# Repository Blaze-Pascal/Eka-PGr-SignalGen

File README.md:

# Eka-PGr-SignalGen

Eka-PGr-SignalGen is a project designed for signal generation circuits, featuring schematic and PCB design using KiCad and simulations in LTSpice. It includes a Bill of Materials for easy component sourcing.
Features:

    KiCad project files for PCB design
    LTSpice simulation files
    BOM generation for parts

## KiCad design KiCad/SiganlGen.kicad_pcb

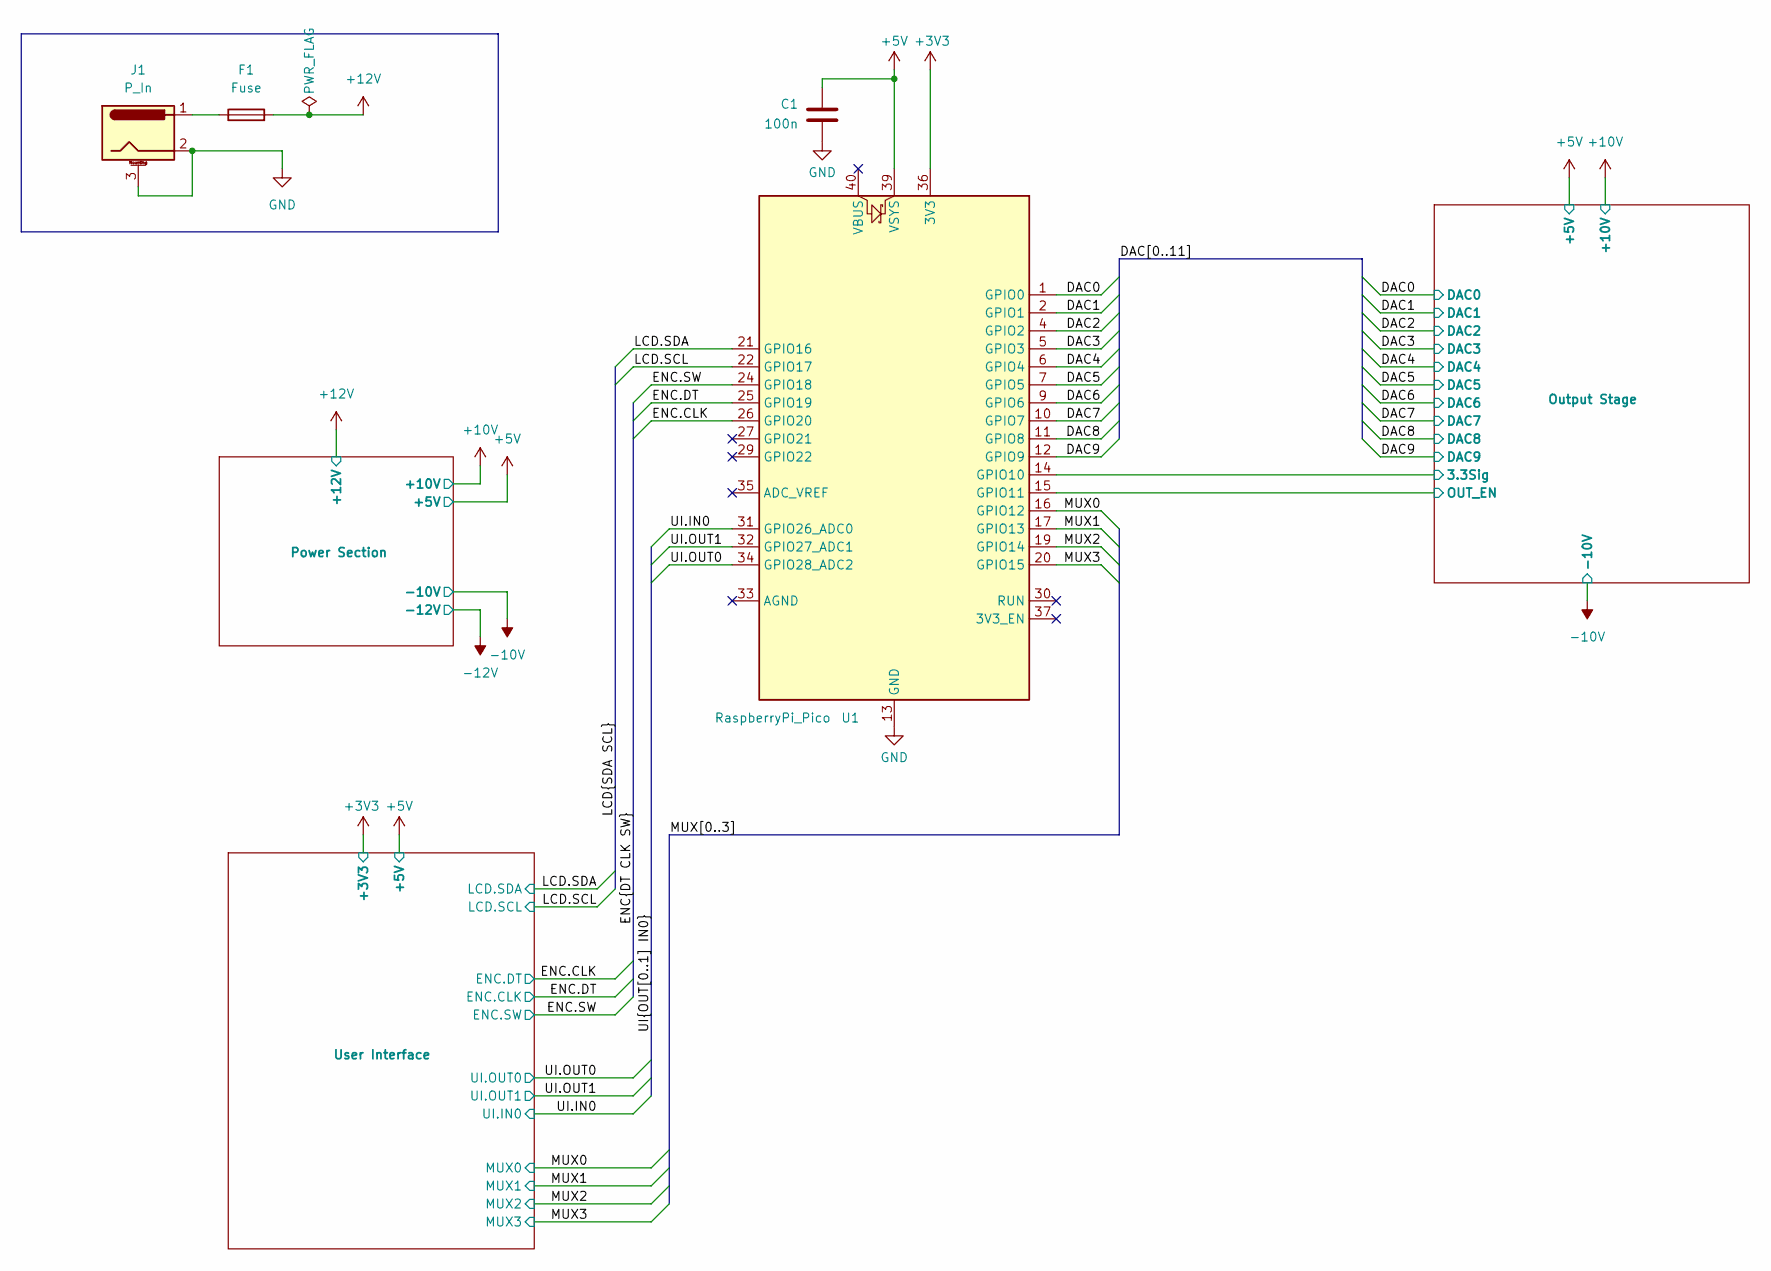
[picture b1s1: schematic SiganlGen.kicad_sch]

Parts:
C1: 100n; C_0805_2012Metric_Pad1.18x1.45mm_HandSolder
F1: Fuse; Fuseholder_Clip-5x20mm_Keystone_3517_Inline_P23.11x6.76mm_D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
J1: P_In; BarrelJack_Horizontal
U1: RaspberryPi_Pico; RaspberryPi_Pico_Common

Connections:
+3V3: U1.36 (3V3); also elsewhere on the board
+5V: C1.1, U1.39 (VSYS); also elsewhere on the board
+12V: F1.2; also elsewhere on the board
/DAC0: U1.1 (GPIO0); also elsewhere on the board
/DAC1: U1.2 (GPIO1); also elsewhere on the board
/DAC2: U1.4 (GPIO2); also elsewhere on the board
/DAC3: U1.5 (GPIO3); also elsewhere on the board
/DAC4: U1.6 (GPIO4); also elsewhere on the board
/DAC5: U1.7 (GPIO5); also elsewhere on the board
/DAC6: U1.9 (GPIO6); also elsewhere on the board
/DAC7: U1.10 (GPIO7); also elsewhere on the board
/DAC8: U1.11 (GPIO8); also elsewhere on the board
/DAC9: U1.12 (GPIO9); also elsewhere on the board
/ENC.CLK: U1.26 (GPIO20); also elsewhere on the board
/ENC.DT: U1.25 (GPIO19); also elsewhere on the board
/ENC.SW: U1.24 (GPIO18); also elsewhere on the board
/LCD.SCL: U1.22 (GPIO17); also elsewhere on the board
/LCD.SDA: U1.21 (GPIO16); also elsewhere on the board
/MUX0: U1.16 (GPIO12); also elsewhere on the board
/MUX1: U1.17 (GPIO13); also elsewhere on the board
/MUX2: U1.19 (GPIO14); also elsewhere on the board
/MUX3: U1.20 (GPIO15); also elsewhere on the board
/Output Stage/3.3Sig: U1.14 (GPIO10); also elsewhere on the board
/Output Stage/OUT_EN: U1.15 (GPIO11); also elsewhere on the board
/UI.IN0: U1.31 (GPIO26_ADC0); also elsewhere on the board
/UI.OUT0: U1.34 (GPIO28_ADC2); also elsewhere on the board
/UI.OUT1: U1.32 (GPIO27_ADC1); also elsewhere on the board
GND: C1.2, J1.2, J1.3 (MountPin), U1.3 (GND), U1.8 (GND), U1.13 (GND), U1.18 (GND), U1.23 (GND), U1.28 (GND), U1.38 (GND); also elsewhere on the board
unnamed: F1.1, J1.1

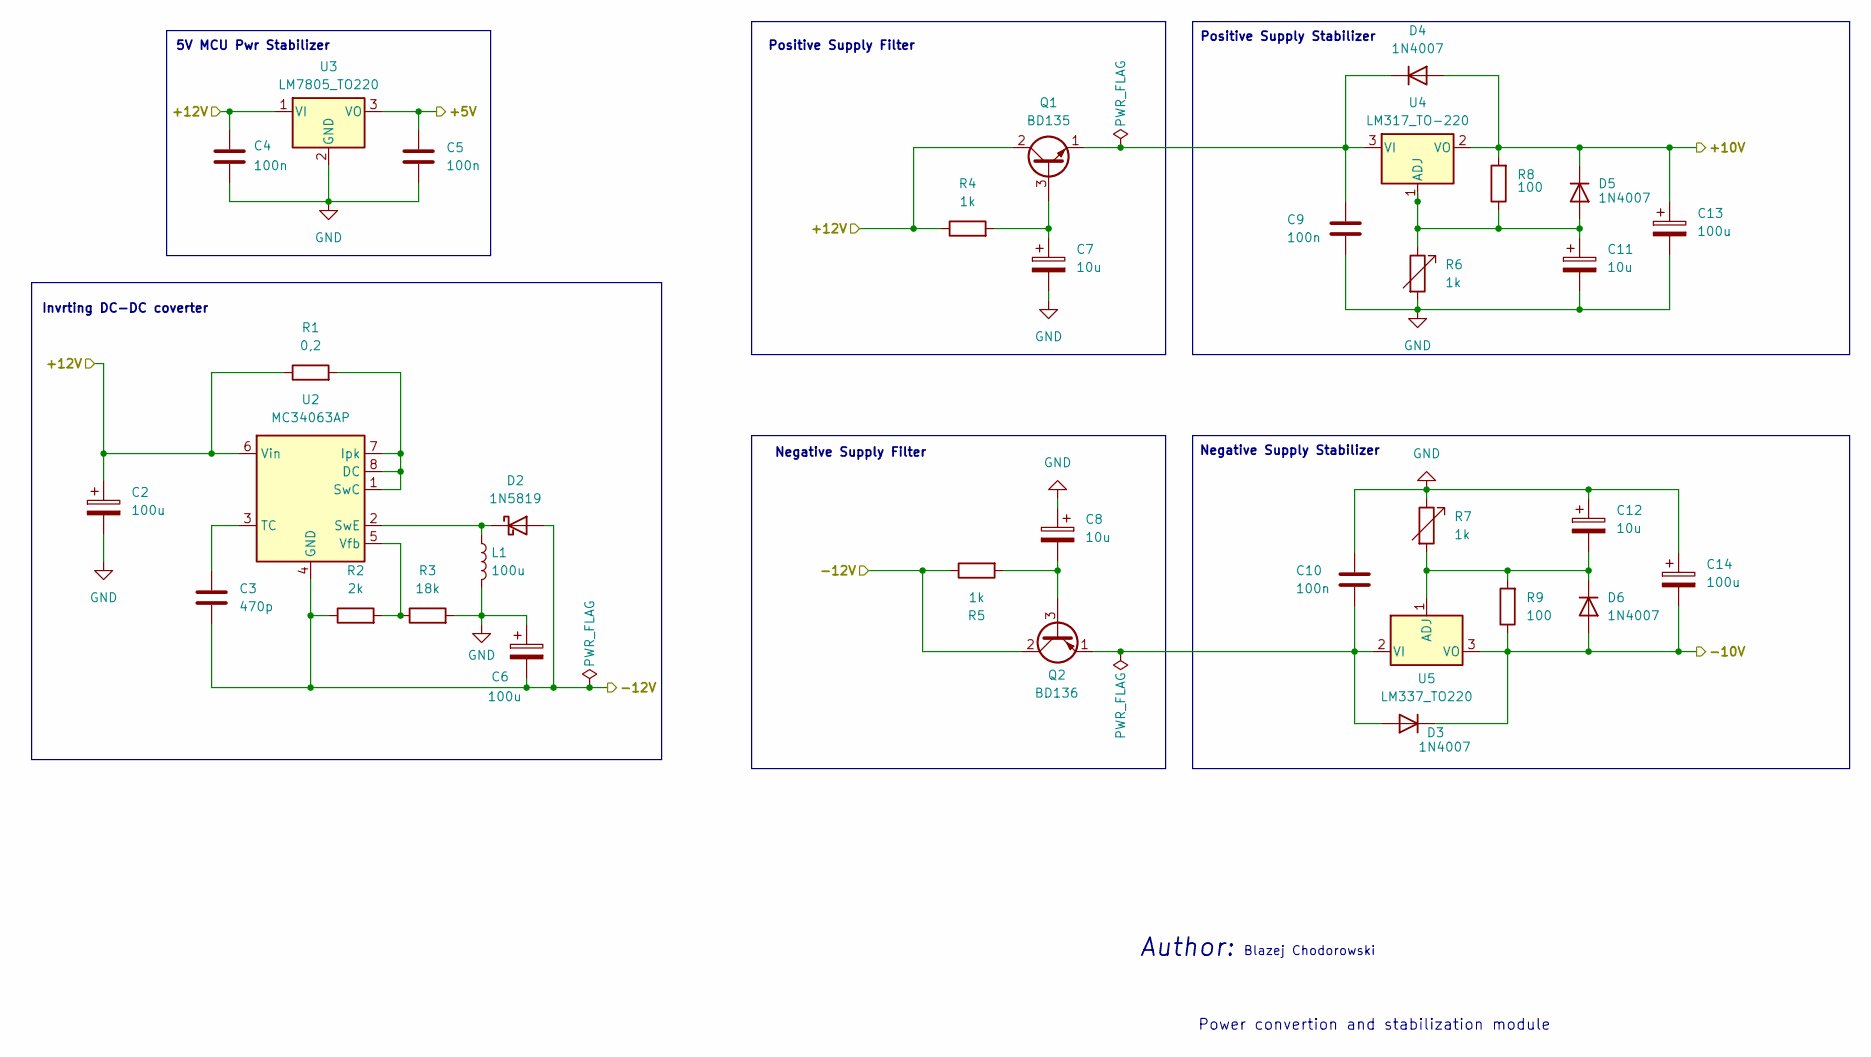
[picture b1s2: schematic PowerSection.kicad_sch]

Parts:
C2, C6, C13, C14: 100u; CP_Radial_D5.0mm_P2.50mm
C3: 470p; C_0805_2012Metric_Pad1.18x1.45mm_HandSolder
C4, C5, C9, C10: 100n; C_0805_2012Metric_Pad1.18x1.45mm_HandSolder
C7, C8, C11, C12: 10u; CP_Radial_D5.0mm_P2.00mm
D2: 1N5819; D_DO-41_SOD81_P10.16mm_Horizontal
D3, D4, D5, D6: 1N4007; D_SOD-123F
L1: 100u; L_Radial_D8.7mm_P5.00mm_Fastron_07HCP
Q1: BD135; TO-126-3_Vertical
Q2: BD136; TO-126-3_Vertical
R1: 0,2; R_0805_2012Metric_Pad1.20x1.40mm_HandSolder
R2: 2k; R_0805_2012Metric_Pad1.20x1.40mm_HandSolder
R3: 18k; R_0805_2012Metric_Pad1.20x1.40mm_HandSolder
R4, R5: 1k; R_0805_2012Metric_Pad1.20x1.40mm_HandSolder
R6, R7: 1k; Potentiometer_Bourns_TC33X_Vertical
R8, R9: 100; R_0805_2012Metric_Pad1.20x1.40mm_HandSolder
U2: MC34063AP; DIP-8_W7.62mm_Socket_LongPads
U3: LM7805_TO220; TO-220-3_Horizontal_TabDown
U4: LM317_TO-220; TO-220-3_Vertical
U5: LM337_TO220; TO-220-3_Vertical

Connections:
+5V: C5.1, U3.3 (VO); also elsewhere on the board
+10V: C13.1, D4.2 (A), D5.1 (K), R8.2, U4.2 (VO); also elsewhere on the board
+12V: C2.1, C4.1, Q1.2 (C), R1.1, R4.1, U2.6 (Vin), U3.1 (VI); also elsewhere on the board
-10V: C14.2, D3.1 (K), D6.2 (A), R9.1, U5.3 (VO); also elsewhere on the board
-12V: C3.2, C6.2, D2.2 (A), Q2.2 (C), R2.1, R5.1, U2.4 (GND)
GND: C2.2, C4.2, C5.2, C6.1, C7.2, C8.1, C9.2, C10.1, C11.2, C12.1, C13.2, C14.1, L1.2, R3.2, R6.2, R7.1, U3.2 (GND); also elsewhere on the board
unnamed: D2.1 (K), L1.1, U2.2 (SwE)
unnamed: C10.2, D3.2 (A), Q2.1 (E), U5.2 (VI)
unnamed: C9.1, D4.1 (K), Q1.1 (E), U4.3 (VI)
unnamed: C11.1, D5.2 (A), R6.1, R8.1, U4.1 (ADJ)
unnamed: C12.2, D6.1 (K), R7.2, R9.2, U5.1 (ADJ)
unnamed: C7.1, Q1.3 (B), R4.2
unnamed: C8.2, Q2.3 (B), R5.2
unnamed: R1.2, U2.1 (SwC), U2.7 (Ipk), U2.8 (DC)
unnamed: C3.1, U2.3 (TC)
unnamed: R2.2, R3.1, U2.5 (Vfb)

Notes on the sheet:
Author:
Positive Supply Filter
Blazej Chodorowski
Power convertion and stabilization module
5V MCU Pwr Stabilizer
Positive Supply Stabilizer
Invrting DC-DC coverter
Negative Supply Stabilizer
Negative Supply Filter

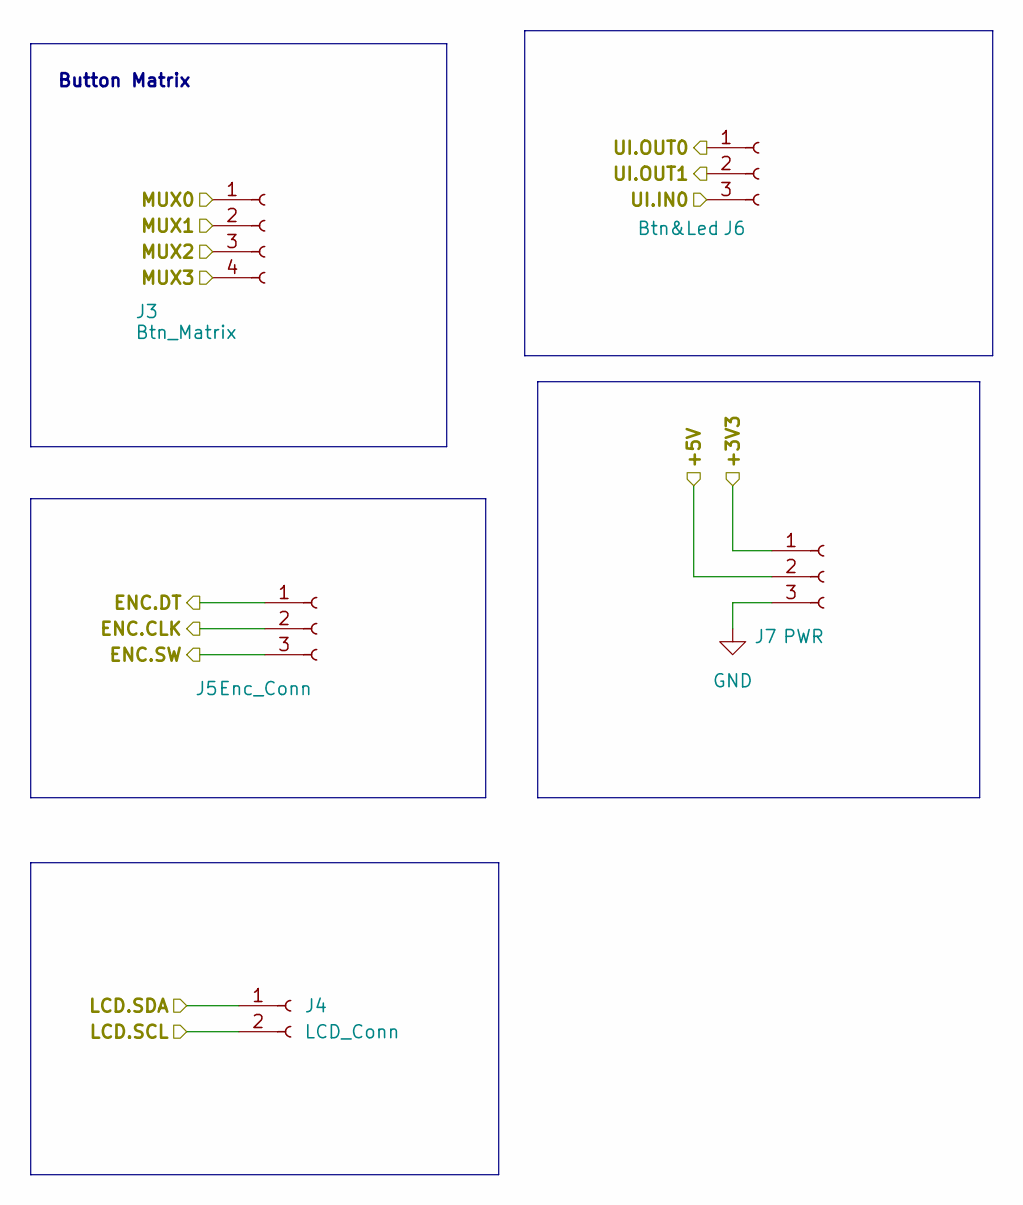
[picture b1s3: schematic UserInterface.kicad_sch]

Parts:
J3: Btn_Matrix; PinSocket_1x04_P2.54mm_Vertical
J4: LCD_Conn; PinHeader_1x02_P2.54mm_Vertical
J5: Enc_Conn; PinHeader_1x03_P2.54mm_Vertical
J6: Btn&Led; PinHeader_1x03_P2.54mm_Vertical
J7: PWR; PinHeader_1x03_P2.54mm_Vertical

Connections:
+3V3: J7.1; also elsewhere on the board
+5V: J7.2; also elsewhere on the board
/ENC.CLK: J5.1; also elsewhere on the board
/ENC.DT: J5.2; also elsewhere on the board
/ENC.SW: J5.3; also elsewhere on the board
/LCD.SCL: J4.2; also elsewhere on the board
/LCD.SDA: J4.1; also elsewhere on the board
/MUX0: J3.1; also elsewhere on the board
/MUX1: J3.2; also elsewhere on the board
/MUX2: J3.3; also elsewhere on the board
/MUX3: J3.4; also elsewhere on the board
/UI.IN0: J6.3; also elsewhere on the board
/UI.OUT0: J6.1; also elsewhere on the board
/UI.OUT1: J6.2; also elsewhere on the board
GND: J7.3; also elsewhere on the board

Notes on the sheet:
Button Matrix

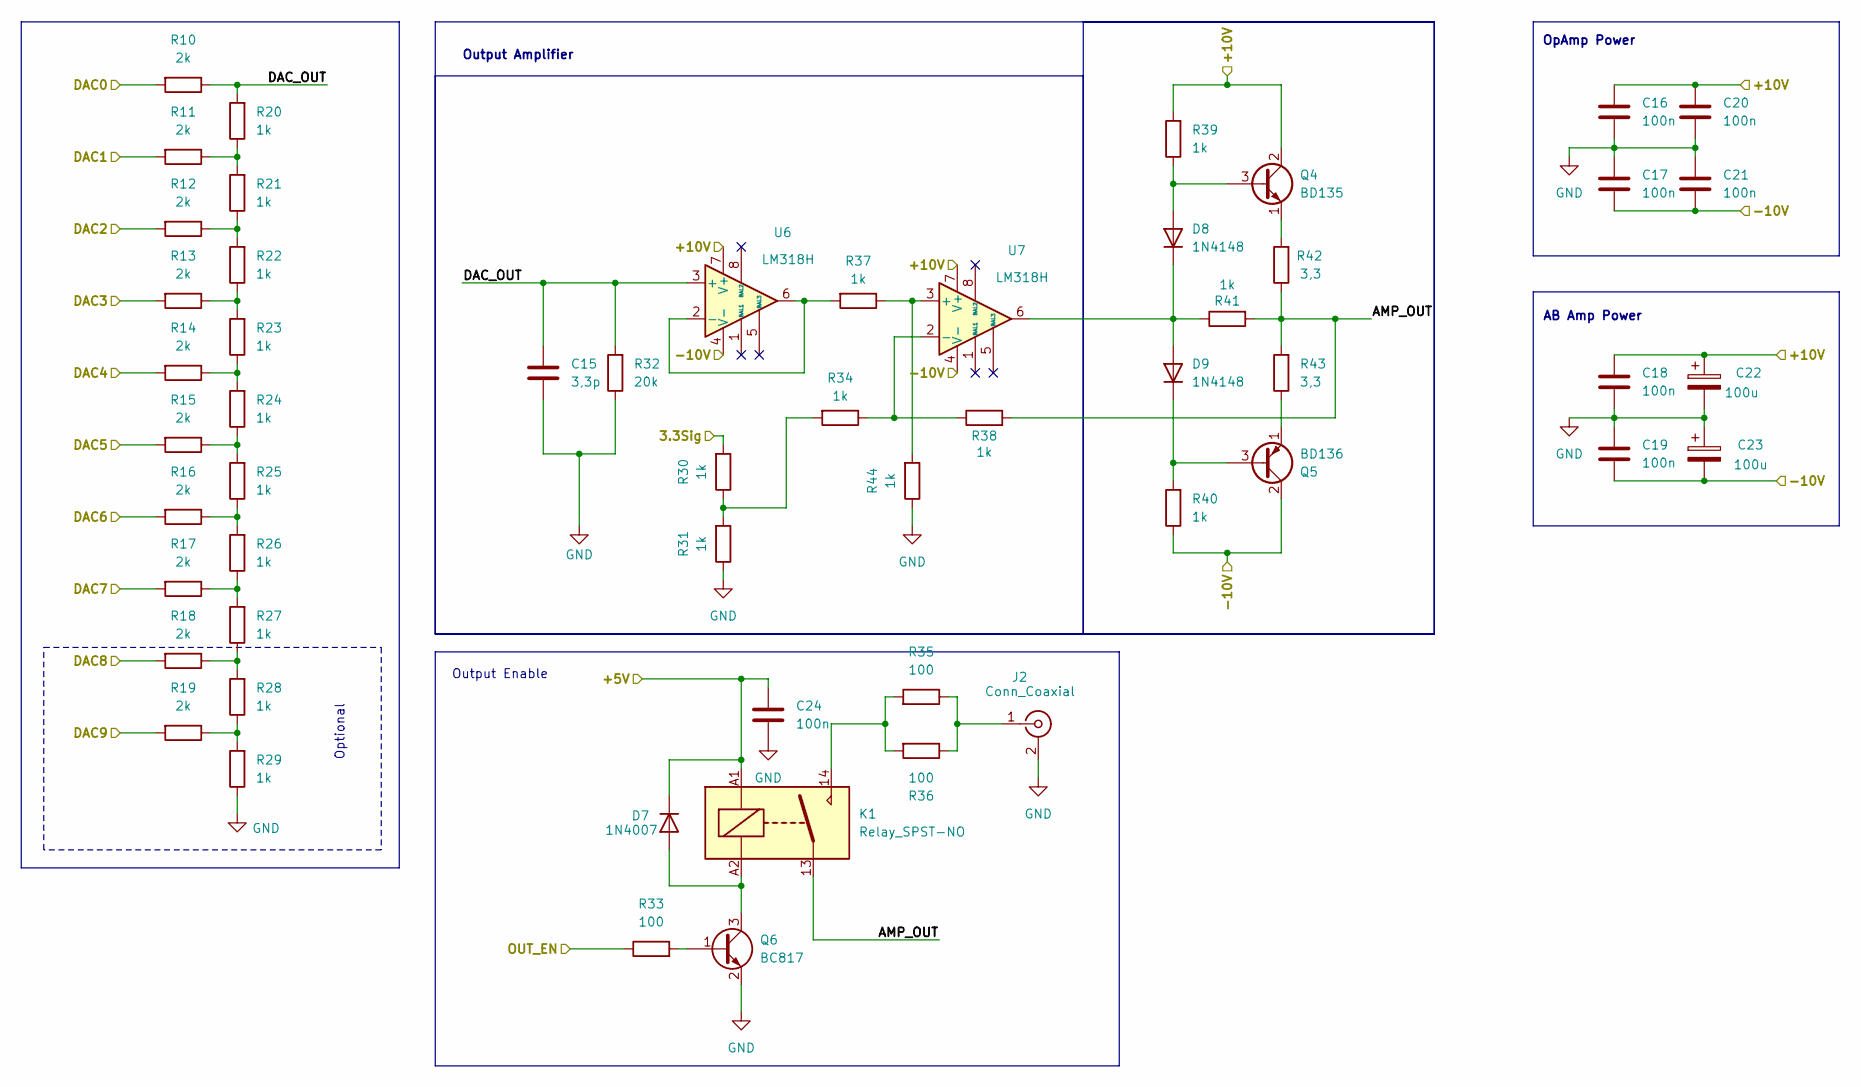
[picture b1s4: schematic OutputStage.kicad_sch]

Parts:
C15: 3,3p; C_0805_2012Metric_Pad1.18x1.45mm_HandSolder
C16, C17, C18, C19, C20, C21, C24: 100n; C_0805_2012Metric_Pad1.18x1.45mm_HandSolder
C22, C23: 100u; CP_Radial_D5.0mm_P2.50mm
D7: 1N4007; D_SOD-123F
D8, D9: 1N4148; Nexperia_CFP3_SOD-123W
J2: Conn_Coaxial; BNC_Amphenol_B6252HB-NPP3G-50_Horizontal
K1: Relay_SPST-NO; Relay_SPST_SANYOU_SRD_Series_Form_B
Q4: BD135; TO-126-3_Vertical
Q5: BD136; TO-126-3_Vertical
Q6: BC817; SOT-23_Handsoldering
R10, R11, R12, R13, R14, R15, R16, R17, R18, R19: 2k; R_0805_2012Metric_Pad1.20x1.40mm_HandSolder
R20, R21, R22, R23, R24, R25, R26, R27, R28, R29, R30, R31, R34, R37, R38, R39, R40, R41, R44: 1k; R_0805_2012Metric_Pad1.20x1.40mm_HandSolder
R32: 20k; R_0805_2012Metric_Pad1.20x1.40mm_HandSolder
R33: 100; R_0805_2012Metric_Pad1.20x1.40mm_HandSolder
R35, R36: 100; R_2512_6332Metric_Pad1.40x3.35mm_HandSolder
R42, R43: 3,3; R_2512_6332Metric_Pad1.40x3.35mm_HandSolder
U6, U7: LM318H; DIP-8_W7.62mm

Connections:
+5V: C24.1, D7.1 (K), K1.A1; also elsewhere on the board
+10V: C16.1, C18.1, C20.1, C22.1, Q4.2 (C), R39.2, U6.7 (V+), U7.7 (V+); also elsewhere on the board
-10V: C17.2, C19.2, C21.2, C23.2, Q5.2 (C), R40.1, U6.4 (V-), U7.4 (V-); also elsewhere on the board
/DAC0: R10.2; also elsewhere on the board
/DAC1: R11.2; also elsewhere on the board
/DAC2: R12.2; also elsewhere on the board
/DAC3: R13.2; also elsewhere on the board
/DAC4: R14.2; also elsewhere on the board
/DAC5: R15.2; also elsewhere on the board
/DAC6: R16.2; also elsewhere on the board
/DAC7: R17.2; also elsewhere on the board
/DAC8: R18.2; also elsewhere on the board
/DAC9: R19.2; also elsewhere on the board
/Output Stage/3.3Sig: R30.2; also elsewhere on the board
/Output Stage/AMP_OUT: K1.13, R38.2, R41.2, R42.1, R43.2
/Output Stage/DAC_OUT: C15.1, R10.1, R20.2, R32.2, U6.3 (+)
/Output Stage/OUT_EN: R33.1; also elsewhere on the board
GND: C15.2, C16.2, C17.1, C18.2, C19.1, C20.2, C21.1, C22.2, C23.1, C24.2, J2.2 (Ext), Q6.2 (E), R29.1, R31.1, R32.1, R44.1; also elsewhere on the board
unnamed: D7.2 (A), K1.A2, Q6.3 (C)
unnamed: D8.2 (A), Q4.3 (B), R39.1
unnamed: D8.1 (K), D9.2 (A), R41.1, U7.6
unnamed: D9.1 (K), Q5.3 (B), R40.2
unnamed: J2.1 (In), R35.1, R36.1
unnamed: K1.14, R35.2, R36.2
unnamed: Q4.1 (E), R42.2
unnamed: Q5.1 (E), R43.1
unnamed: Q6.1 (B), R33.2
unnamed: R11.1, R20.1, R21.2
unnamed: R12.1, R21.1, R22.2
unnamed: R13.1, R22.1, R23.2
unnamed: R14.1, R23.1, R24.2
unnamed: R15.1, R24.1, R25.2
unnamed: R16.1, R25.1, R26.2
unnamed: R17.1, R26.1, R27.2
unnamed: R18.1, R27.1, R28.2
unnamed: R19.1, R28.1, R29.2
unnamed: R30.1, R31.2, R34.2
unnamed: R37.2, U6.2 (-), U6.6
unnamed: R37.1, R44.2, U7.3 (+)
unnamed: R34.1, R38.1, U7.2 (-)

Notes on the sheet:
Optional
Output Enable
AB Amp Power
OpAmp Power
Output Amplifier

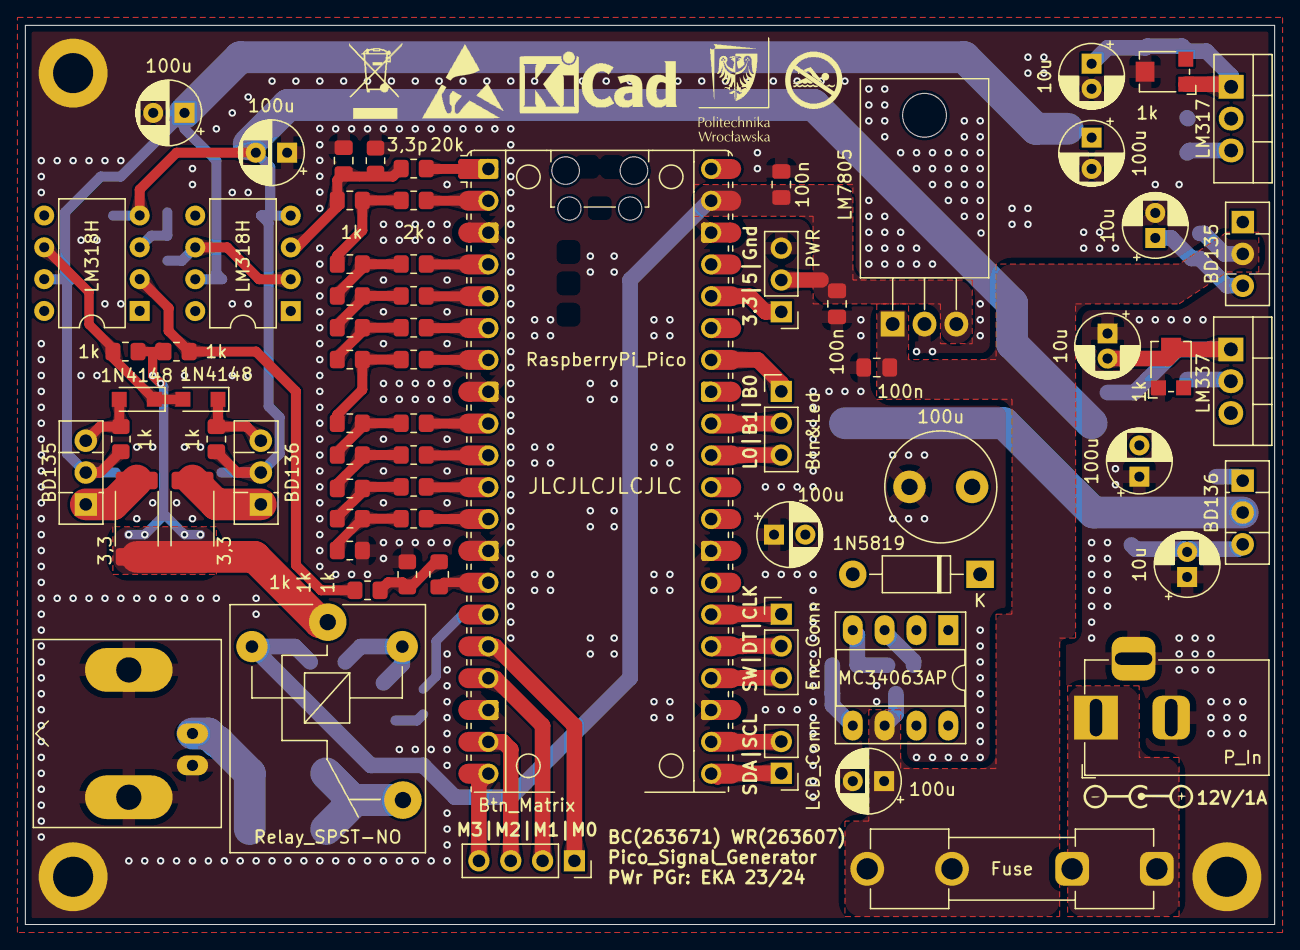
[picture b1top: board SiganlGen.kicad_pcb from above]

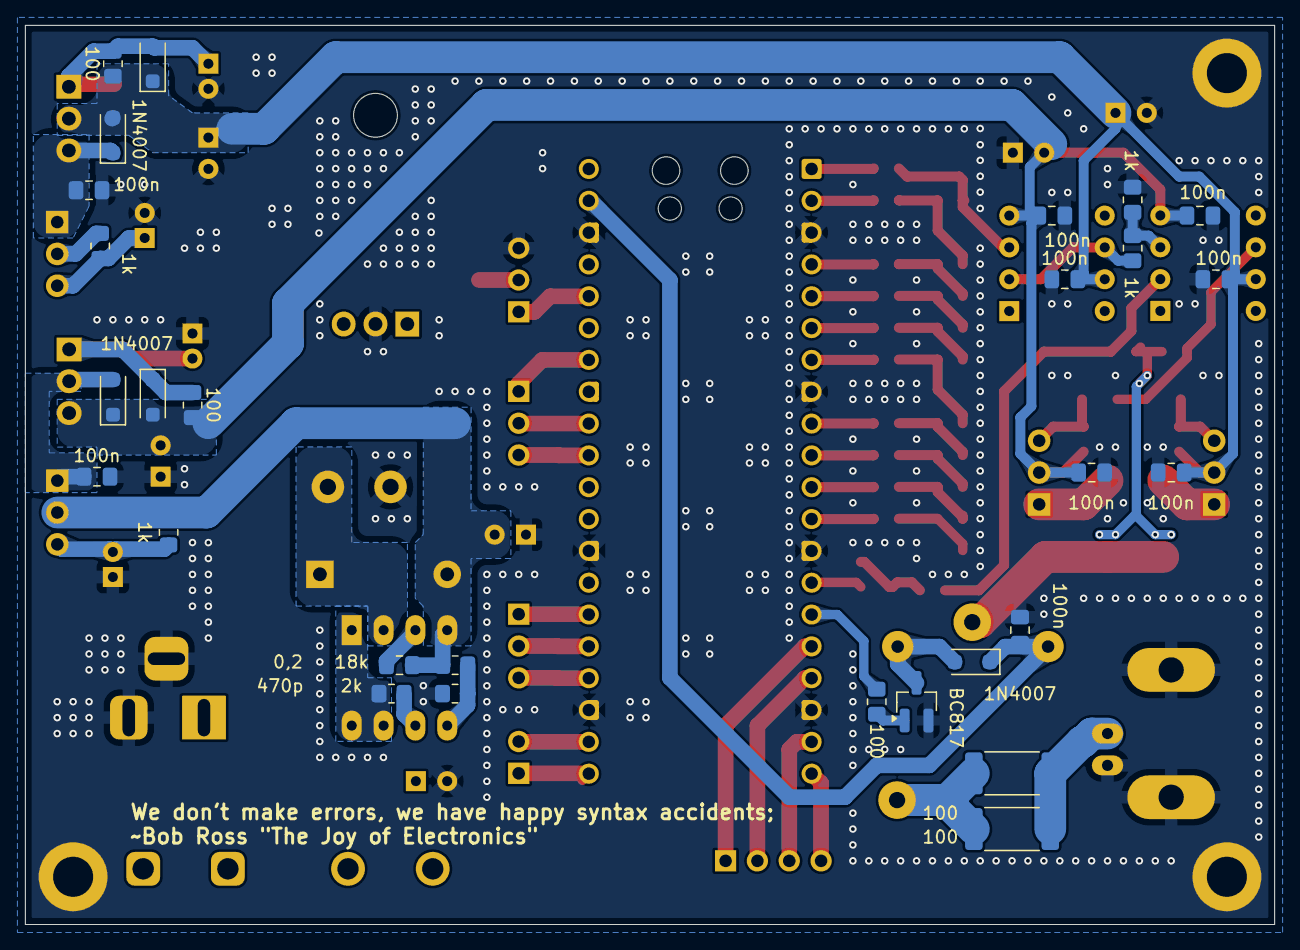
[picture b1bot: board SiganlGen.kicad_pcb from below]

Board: 2 copper layers, 99.7 x 71.8 mm, 98 parts (28 on the bottom side), 66 nets.

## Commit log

2024-04-29 footprints
2024-04-29 dupa
2024-04-29 Delete
2024-04-29 Added program folders
2024-04-29 DAC Simulation file
2024-04-29 Partition schematic to different sheets
2024-04-29 Added elements values
2024-04-29 Filled in schematic
2024-04-29 Added footprints
2024-05-02 minor changes
2024-05-02 mux in ui
2024-05-03 UI connections to uC
2024-05-03 First DAC layout, rough board layout
2024-05-04 bom, changed lm7810 to lm317
2024-05-05 minor changes, testing
2024-05-05 Added protection elements and an additional input connector
2024-05-05 Added/changed footprints
2024-05-05 Changed stabilizator capacitors values
2024-05-05 Changed footprints, arrangement of elements on pcb
2024-05-06 Tidied up schematic, changed footprints
2024-05-06 Alfa version of PCB design
2024-05-06 PCB update
2024-05-06 PCB design
2024-05-09 output sim, filter sim, filter sch, output change
2024-05-09 Updated footprints
2024-05-10 Final PCB version (probably)
2024-05-10 removed solder mask under lm7805
2024-05-10 Update pcb
2024-05-10 silkscreen art
